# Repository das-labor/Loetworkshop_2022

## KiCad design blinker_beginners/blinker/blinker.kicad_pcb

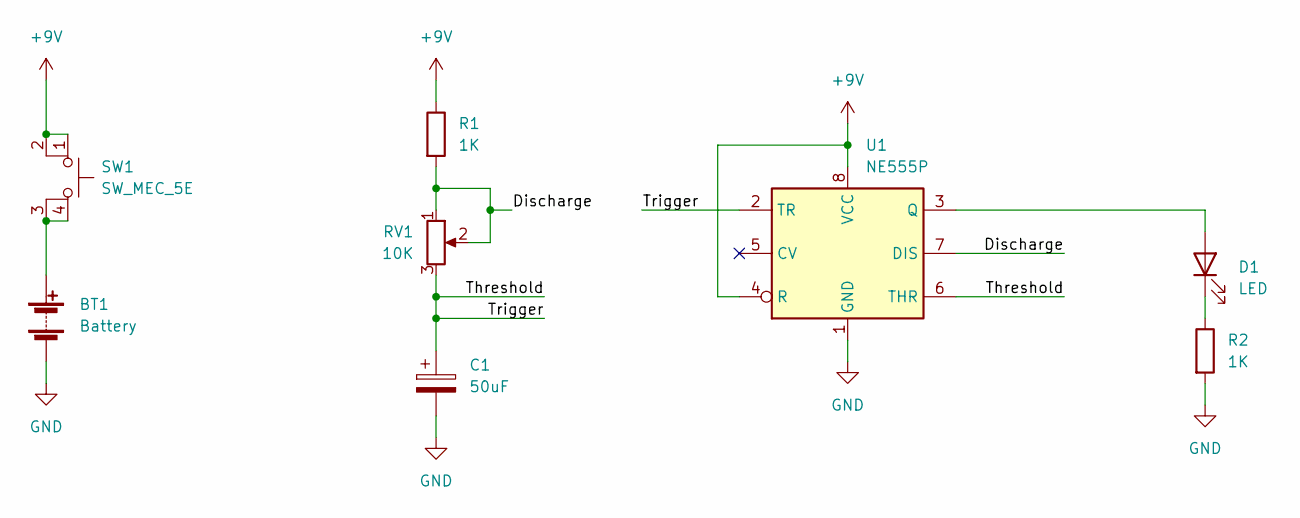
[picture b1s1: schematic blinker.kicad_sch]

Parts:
BT1: Battery; PinHeader_1x02_P2.54mm_Vertical
C1: 50uF; CP_Radial_D5.0mm_P2.00mm
D1: LED; LED_D5.0mm
R1, R2: 1K; R_Axial_DIN0207_L6.3mm_D2.5mm_P7.62mm_Horizontal
RV1: 10K; Potentiometer_Piher_PT-15-V02_Vertical
SW1: SW_MEC_5E; SW_PUSH_6mm
U1: NE555P; DIP-8_W7.62mm

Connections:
+9V: R1.1, SW1.1, SW1.2, U1.4 (R), U1.8 (VCC)
/Discharge: R1.2, RV1.1, RV1.2, U1.7 (DIS)
/Threshold: C1.1, RV1.3, U1.2 (TR), U1.6 (THR)
GND: BT1.2 (-), C1.2, R2.2, U1.1 (GND)
unnamed: BT1.1 (+), SW1.3 (K), SW1.4 (A)
unnamed: D1.1 (K), R2.1
unnamed: D1.2 (A), U1.3 (Q)

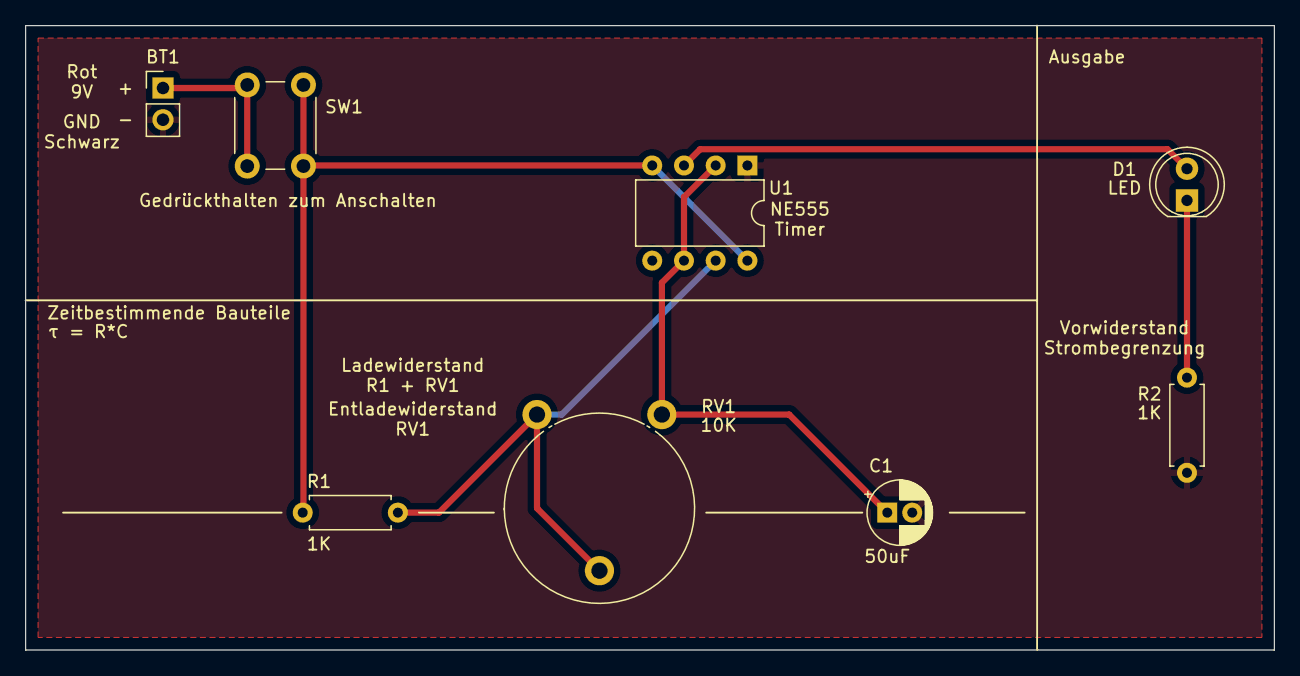
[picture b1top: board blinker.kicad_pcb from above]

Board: 2 copper layers, 100.0 x 50.0 mm, 8 parts (0 on the bottom side), 7 nets.

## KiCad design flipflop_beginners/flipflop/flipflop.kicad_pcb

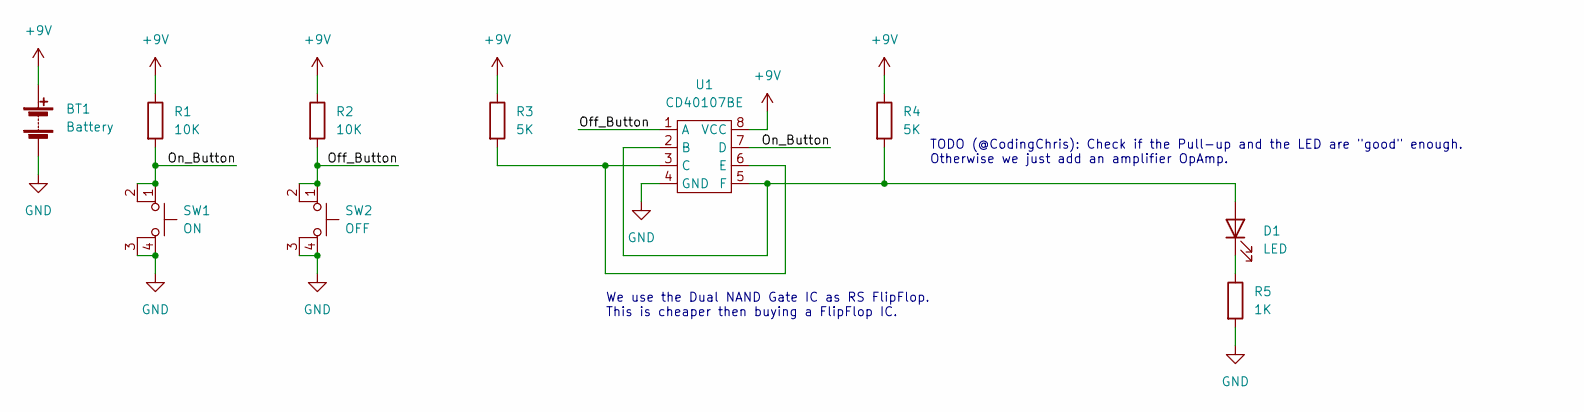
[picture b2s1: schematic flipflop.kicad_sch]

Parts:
BT1: Battery; PinHeader_1x02_P2.54mm_Vertical
D1: LED; LED_D5.0mm
R1, R2: 10K; R_Axial_DIN0207_L6.3mm_D2.5mm_P7.62mm_Horizontal
R3, R4: 5K; R_Axial_DIN0207_L6.3mm_D2.5mm_P7.62mm_Horizontal
R5: 1K; R_Axial_DIN0207_L6.3mm_D2.5mm_P7.62mm_Horizontal
SW1: ON; SW_PUSH_6mm
SW2: OFF; SW_PUSH_6mm
U1: CD40107BE; DIP-8_W7.62mm

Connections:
+9V: BT1.1 (+), R1.1, R2.1, R3.1, R4.1, U1.8 (VCC)
/Off_Button: R2.2, SW2.1, SW2.2, U1.1 (A)
/On_Button: R1.2, SW1.1, SW1.2, U1.7 (D)
GND: BT1.2 (-), R5.2, SW1.3 (K), SW1.4 (A), SW2.3 (K), SW2.4 (A), U1.4 (GND)
unnamed: D1.1 (K), R5.1
unnamed: D1.2 (A), R4.2, U1.2 (B), U1.5 (F)
unnamed: R3.2, U1.3 (C), U1.6 (E)

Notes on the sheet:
TODO (@CodingChris): Check if the Pull-up and the LED are "good" enough. Otherwise we just add an amplifier OpAmp.
We use the Dual NAND Gate IC as RS FlipFlop. This is cheaper then buying a FlipFlop IC.

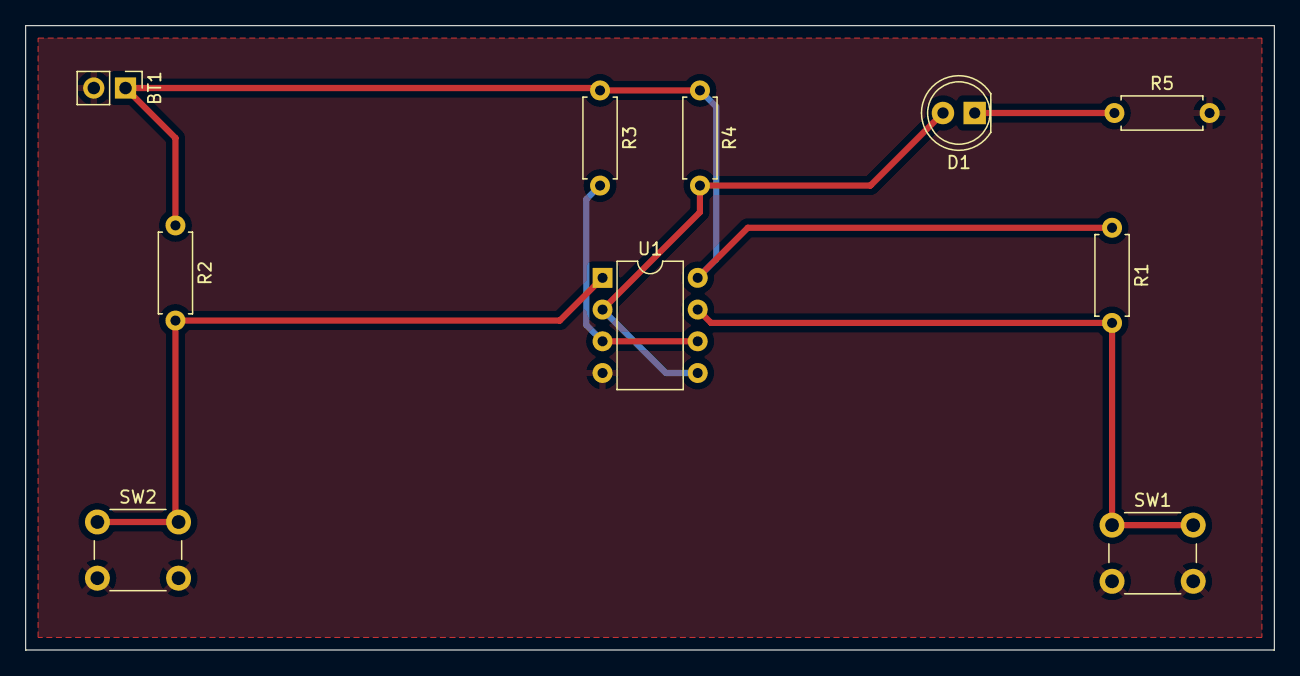
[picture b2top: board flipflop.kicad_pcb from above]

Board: 2 copper layers, 100.0 x 50.0 mm, 10 parts (0 on the bottom side), 7 nets.

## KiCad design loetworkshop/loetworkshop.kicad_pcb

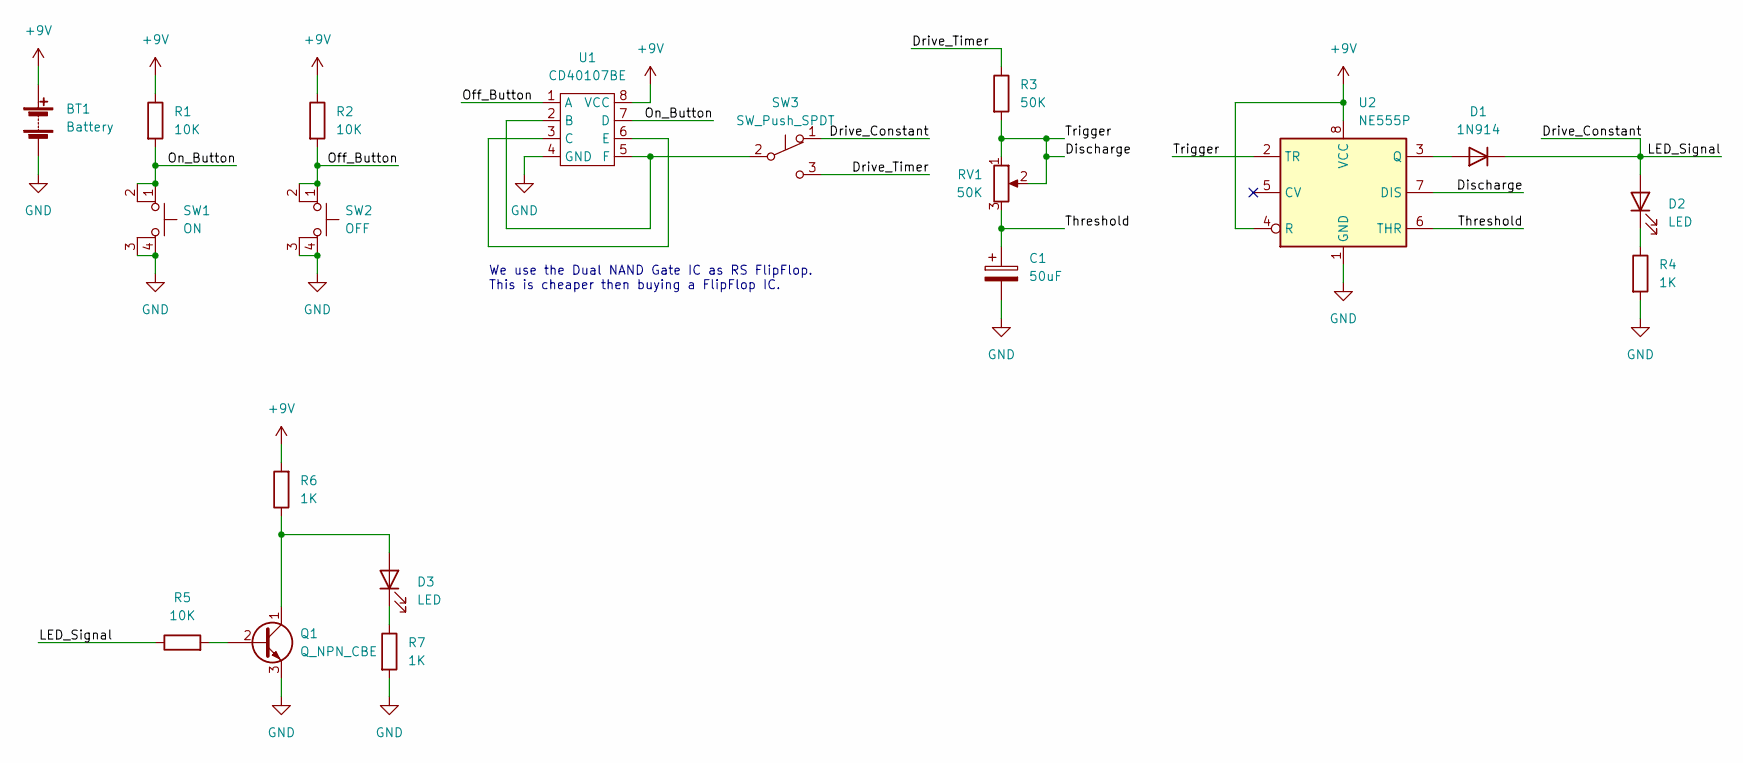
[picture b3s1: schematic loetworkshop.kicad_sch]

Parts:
BT1: Battery; PinHeader_1x02_P2.54mm_Vertical
C1: 50uF; CP_Radial_D5.0mm_P2.00mm
D1: 1N914; D_DO-35_SOD27_P7.62mm_Horizontal
D2, D3: LED; LED_D5.0mm
Q1: Q_NPN_CBE; TO-92
R1, R2, R5: 10K; R_Axial_DIN0207_L6.3mm_D2.5mm_P7.62mm_Horizontal
R3: 50K; R_Axial_DIN0207_L6.3mm_D2.5mm_P7.62mm_Horizontal
R4, R6, R7: 1K; R_Axial_DIN0207_L6.3mm_D2.5mm_P7.62mm_Horizontal
RV1: 50K; Potentiometer_Piher_PT-15-V02_Vertical
SW1: ON; SW_PUSH_6mm
SW2: OFF; SW_PUSH_6mm
SW3: SW_Push_SPDT; PinHeader_1x03_P2.54mm_Vertical
U1: CD40107BE; DIP-8_W7.62mm
U2: NE555P; DIP-8_W7.62mm_InvertedDualRow

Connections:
+9V: BT1.1 (+), R1.1, R2.1, R6.2, U1.8 (VCC), U2.4 (R), U2.8 (VCC)
/Discharge: R3.2, RV1.1, RV1.2, U2.2 (TR), U2.7 (DIS)
/Drive_Constant: D1.1 (K), D2.2 (A), R5.1, SW3.1 (A)
/Drive_Timer: R3.1, SW3.3 (C)
/Off_Button: R2.2, SW2.1, SW2.2, U1.1 (A)
/On_Button: R1.2, SW1.1, SW1.2, U1.7 (D)
/Threshold: C1.1, RV1.3, U2.6 (THR)
GND: BT1.2 (-), C1.2, Q1.3 (E), R4.2, R7.2, SW1.3 (K), SW1.4 (A), SW2.3 (K), SW2.4 (A), U1.4 (GND), U2.1 (GND)
unnamed: D1.2 (A), U2.3 (Q)
unnamed: D2.1 (K), R4.1
unnamed: D3.1 (K), R7.1
unnamed: D3.2 (A), Q1.1 (C), R6.1
unnamed: Q1.2 (B), R5.2
unnamed: SW3.2 (B), U1.2 (B), U1.5 (F)
unnamed: U1.3 (C), U1.6 (E)

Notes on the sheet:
We use the Dual NAND Gate IC as RS FlipFlop. This is cheaper then buying a FlipFlop IC.

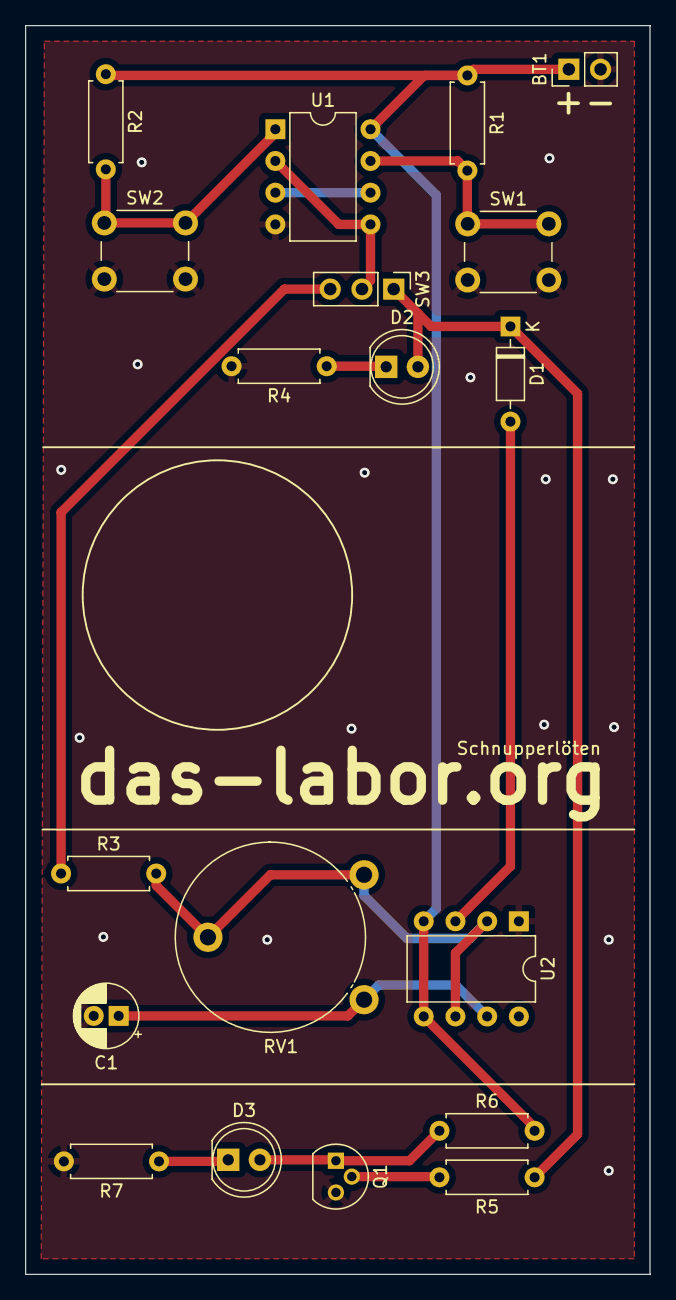
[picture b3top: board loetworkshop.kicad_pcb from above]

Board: 2 copper layers, 50.0 x 100.0 mm, 19 parts (0 on the bottom side), 15 nets.

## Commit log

2022-02-20 Initial Project Setup
2022-02-20 Design board
2022-02-21 added third soldering challenge
2022-02-23 new pcb layout
2022-02-24 rev 1
2022-02-24 rev 1.1 - fixed IC Pinout in the Footprint
2022-02-24 rev 1.2
2022-02-24 rev 1.3 - more footprint fixes
2022-03-05 Changes to accomodate issues in NAND Driver Design
2022-03-05 Blinker Project Splitoff
2022-03-05 flipflop
2022-03-06 flipflop pcb redesign
2022-03-11 Hold Enable Button for Blink
2022-03-11 fixes
2022-03-11 3rd workshop - analog inverter opamp
2022-03-14 pcb design for board rev 1
2022-03-19 qr code maybe?
